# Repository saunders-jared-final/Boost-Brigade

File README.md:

# Boost Brigade — solar power shuffler (S-PPC) string

Adaptive control of serial partial-power converters ("power shufflers") for
MPPT under partial shading. QUT EGH490 capstone: control stream (this repo's
firmware/control/simulation) + hardware stream (Version 0 PCB).

**Current goal (due Fri 16 Oct 2026): carpark experiment** — 3 × 150 W panels,
2 shufflers on the Version 0 board, EcoFlow DELTA 2 Max as the string MPPT
load, closed-loop module equalisation on the Nucleo-G474RE, telemetry on
Grafana via the Raspberry Pi pod. Day-by-day plan: `0_Documentation/PLAN.md`.

## Layout

| Folder | What |
|---|---|
| `0_Documentation/` | proposals, progress reports, UI pod wiring, **`telemetry.md`** (Nucleo↔Pi contract), plan, experiment checklist |
| `1_Datasheets/` | INA239, TMCS1126, 1ED3140, EcoFlow, LM5180 calculator |
| `2_Qspice/` | switching-level models; `Claude's outputs/PCB_Baseline/` is the scripted baseline (`gen_shuffler.py` → stages S1–S8b, `run_baseline.py`); closed-loop C-block stage S9 to come |
| `3_Analytical/` | notebooks + design log (`shuffler_notebooks/DESIGN_LOG.md`) and the early MATLAB control-design lineage |
| `4_Simulink/` | test ladder: `1_MIL` (4-mod validated model), `2_SIL` (C Caller model + **host build/tests of the C core**), **`3_Carpark_3mod`** (3-module scripts + model-edit checklist) |
| `5_Kicad/` | `Version 0 project/` (schematic, PCB, gerbers) + `libs/` (all part libraries; project-relative lib tables) |
| `6_RTOS/` | STM32G474 firmware (CubeMX + CMake) and **`ctrl_core/`**, the single copy of the control-stack C shared by SIL, QSPICE and firmware; `ctrl_core/params/` holds the JSON gain file and generators |
| `7_Pi/` | Raspberry Pi pod: InfluxDB + Grafana compose, serial bridge, IR/LCD/LED service, bench tools |

## Gain flow (one source, three harnesses)

```
Simulink ident (4_Simulink/3_Carpark_3mod/shuffler_string_ident.m)
   └─> 6_RTOS/ctrl_core/params/shuffler_params.json   (M, Ts, thresholds)
         └─> gen_params.py / export_params.m  ->  6_RTOS/ctrl_core/params.h
               ├─> SIL: C Caller blocks + golden replay + unit tests (4_Simulink/2_SIL.../firmware)
               ├─> QSPICE: shuffler_ctrl.dll C-block, stage S9 (2_Qspice)
               └─> firmware: 10 kHz control ISR on the Nucleo (6_RTOS)
```

Hardware facts that shape the control configuration (verified in `5_Kicad`):
- 3 panels / 2 converters; HRTIM pins PA8-11 (S1 A/B high/low) and PB12-15 (S2); hall sensors PA0 ILA_1, PA4 ILB_1, PA1 ILA_2, PC1 ILB_2; INA239 ×3 on SPI3 (CS PA7, PB6, PC7).
- The INA239s read bus voltage only (shunt inputs shorted): module currents are **reconstructed** from the inductor currents and duties (`ctrl_core/shuffler_recon.c`); the string current is an unobservable common offset that the supervisor's deficit term cancels. String-level MPPT is the EcoFlow's job (`en_mppt = 0` in firmware).
- U10 (panel-1 voltage) sits behind a mis-wired ISO7762: rework required for closed loop on converter 1.
- 1ED3140 drivers have no fault pins and add no dead time; dead time (200 ns, HRTIM) and over-current trips are firmware.

## Quick starts

Host tests of the control core (WSL):
```sh
cd 4_Simulink/2_SIL_Software_In_The_Loop/firmware && cmake -B build && cmake --build build && ctest --test-dir build --output-on-failure
```
Regenerate gains after an identification: `python3 6_RTOS/ctrl_core/params/gen_params.py`
(or `export_params` in MATLAB). Preset `params/mil4_params.json` reproduces the validated 4-module constants.

Firmware build (Windows ST bundle, callable from WSL; paths in `6_RTOS/.vscode/tasks.json`):
```sh
cd 6_RTOS && cmake.exe --preset Debug && cmake.exe --build --preset Debug
STM32_Programmer_CLI.exe -c port=SWD -w build/Debug/Shuffler_1_Open_Loop.elf -rst
```

## Panel reference (150 W hard-frame, 22 V model)

Pm 150 W ±3 %, Vmp 18.28 V, Imp 8.207 A, Voc 22.407 V, Isc 8.721 A, NOCT 45 ±2 °C,
max series fuse 15 A, 1160 × 670 × 30 mm, 9.32 kg, IP67.

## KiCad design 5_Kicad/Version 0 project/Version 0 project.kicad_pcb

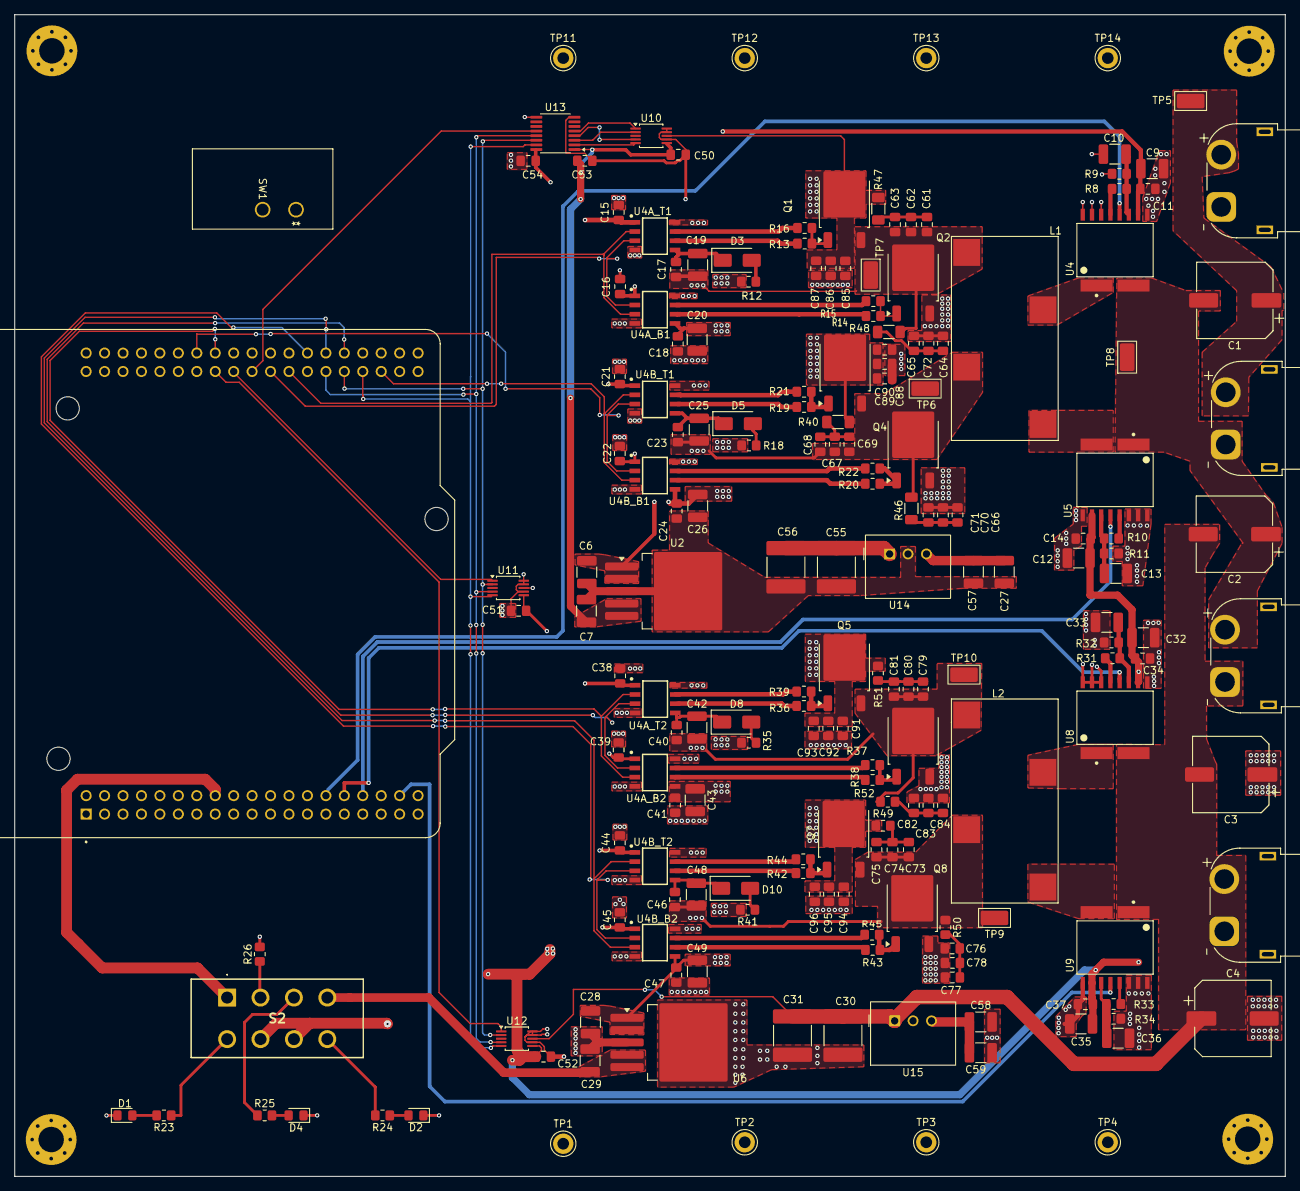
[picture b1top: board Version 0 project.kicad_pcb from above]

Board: 6 copper layers, 175.0 x 160.0 mm, 195 parts (0 on the bottom side), 96 nets.

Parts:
C1, C2: B40910A0137M000; CP_Elec_10x16.5
C3, C4: 130u; CP_Elec_10x16.5
C6, C7, C9, C10, C12, C13, C27, C28, C29, C32, C33, C35, C36, C57, C58, C59: 10uF; C_1210_3225Metric_Pad1.33x2.70mm_HandSolder
C11, C14, C34, C37, C61, C62, C63, C64, C65, C66, C67, C68, C69, C70, C71, C72, C73, C74, C75, C76, C77, C78, C79, C80, C81, C82, C83, C84, C85, C86, C87, C88, C89, C90, C91, C92, C93, C94, C95, C96: 0.1uF; C_0805_2012Metric_Pad1.18x1.45mm_HandSolder
C15, C16, C17, C18, C21, C22, C38, C39, C40, C41, C44, C45, C50, C51, C52, C53, C54: 100n; C_0805_2012Metric_Pad1.18x1.45mm_HandSolder
C19, C20, C25, C26, C42, C43, C48, C49: 10u; C_1210_3225Metric_Pad1.33x2.70mm_HandSolder
C23, C24, C46, C47: 100nF; C_0805_2012Metric_Pad1.18x1.45mm_HandSolder
C30, C31, C55, C56: 10uF; C_2220_5750Metric_Pad1.97x5.40mm_HandSolder
D1: LED_R; LED_0805_2012Metric_Pad1.15x1.40mm_HandSolder
D2: LED_B; LED_0805_2012Metric_Pad1.15x1.40mm_HandSolder
D3, D5, D8, D10: D; D_SMA
D4: LED_G; LED_0805_2012Metric_Pad1.15x1.40mm_HandSolder
H1, H2, H3, H4: MountingHole; MountingHole_3.5mm_Pad_Via
L1, L2: ERUC23-4R1K
Q1, Q2, Q3, Q4, Q5, Q6, Q7, Q8: STD45N10F7; TO-252-3_TabPin2
R8, R10, R26, R31, R33: 1k; R_0805_2012Metric_Pad1.20x1.40mm_HandSolder
R9, R11, R32, R34: 1.5K; R_0805_2012Metric_Pad1.20x1.40mm_HandSolder
R12, R13, R14, R18, R19, R20, R35, R36, R37, R41, R42, R43: 10R; R_0805_2012Metric_Pad1.20x1.40mm_HandSolder
R15, R16, R21, R22, R38, R39, R44, R45, R49, R50, R51, R52: 4.7R; R_0805_2012Metric_Pad1.20x1.40mm_HandSolder
R23, R25: 680; R_0805_2012Metric_Pad1.20x1.40mm_HandSolder
R24: 100; R_0805_2012Metric_Pad1.20x1.40mm_HandSolder
R40, R46, R47, R48: 4.7R; R_1206_3216Metric_Pad1.30x1.75mm_HandSolder
S2: L203011MS02Q
SW1: L101011MS02Q; SW_1MS02Q_CNK
TP1, TP2, TP3, TP4, TP11, TP12, TP13, TP14: TestPoint; TestPoint_Keystone_5010-5014_Multipurpose
TP5, TP6, TP7, TP8, TP9, TP10: TestPoint; TestPoint_Keystone_5019_Miniature_Wide
U1: NUCLEO-G474RE; MODULE_NUCLEO-G474RE
U2, U6: TPS7A4533; TO-263-5_TabPin3
U4, U8: TMCS1126B4AQDVGRQ1; DVG0010A-MFG
U4A_B1, U4A_B2, U4A_T1, U4A_T2, U4B_B1, U4B_B2, U4B_T1, U4B_T2: 1ED3140MU12F; SOIC127P600X175-8N-22-V1
U5, U9: TMCS1126B1AQDVGR; DVG0010A-MFG
U10, U11, U12: INA229; TSSOP-10_3x3mm_P0.5mm
U13: ISO7762QDBQRQ1; SSOP-16_3.9x4.9mm_P0.635mm
U14, U15: 173951275; U_Wurth_WPME-FDSM_17395xx75
XT60_1: PV Connector 1; AMASS_XT60PW-F_1x02_P7.20mm_Horizontal
XT60_2: PV Connector 2; AMASS_XT60PW-F_1x02_P7.20mm_Horizontal
XT60_3: PV Connector 3; AMASS_XT60PW-F_1x02_P7.20mm_Horizontal
XT60_4: PV Connector 4; AMASS_XT60PW-F_1x02_P7.20mm_Horizontal

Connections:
+3V3: C9.1, C11.1, C12.1, C14.1, C32.1, C34.1, C35.1, C37.1, C51.1, C52.1, C54.2, S2.6, S2.7, SW1.1, U4.4 (VS), U5.4 (VS), U8.4 (VS), U9.4 (VS), U11.6 (VS), U12.6 (VS), U13.16 (Vcc2)
/CS1: U1.CN10_15 (PA7), U12.1 (~CS)
/CS2: U1.CN10_17 (PB6), U11.1 (~CS)
/CS3: U1.CN10_19 (PC7), U13.12 (OUTD)
/Floating 3v3: C7.1, C50.1, C53.1, U2.4 (OUT), U2.5 (SENSE), U10.6 (VS), U13.1 (Vcc1)
/Gate Driver 3v3: C15.2, C16.2, C21.2, C22.2, C38.2, C39.2, C44.2, C45.2, SW1.2, U4A_B1.1 (VCC1), U4A_B2.1 (VCC1), U4A_T1.1 (VCC1), U4A_T2.1 (VCC1), U4B_B1.1 (VCC1), U4B_B2.1 (VCC1), U4B_T1.1 (VCC1), U4B_T2.1 (VCC1)
/ILA_1: U1.CN7_28 (PA0), U4.6 (VOUT)
/ILA_2: U1.CN7_30 (PA1), U8.6 (VOUT)
/ILB_1: U1.CN7_32 (PA4), U5.6 (VOUT)
/ILB_2: U1.CN7_36 (PC1/PB9), U9.6 (VOUT)
/LDO 3v3: C29.1, S2.4, U6.4 (OUT), U6.5 (SENSE)
/S1_A_H: U1.CN10_23 (PA8), U4A_B1.3 (IN_N), U4A_T1.2 (IN_P)
/S1_A_L: U1.CN10_21 (PA9), U4A_B1.2 (IN_P), U4A_T1.3 (IN_N)
/S1_B_H: U1.CN10_33 (PA10), U4B_B1.3 (IN_N), U4B_T1.2 (IN_P)
/S1_B_L: U1.CN10_14 (PA11), U4B_B1.2 (IN_P), U4B_T1.3 (IN_N)
/S2_A_H: U1.CN10_16 (PB12), U4A_B2.3 (IN_N), U4A_T2.2 (IN_P)
/S2_A_L: U1.CN10_30 (PB13), U4A_B2.2 (IN_P), U4A_T2.3 (IN_N)
/S2_B_H: U1.CN10_28 (PB14), U4B_B2.3 (IN_N), U4B_T2.2 (IN_P)
/S2_B_L: U1.CN10_26 (PB15), U4B_B2.2 (IN_P), U4B_T2.3 (IN_N)
/SPI MISO: U1.CN10_27 (PB4), U11.4 (MISO), U12.4 (MISO), U13.13 (OUTC)
/SPI MOSI: U1.CN10_29 (PB5), U11.2 (MOSI), U12.2 (MOSI), U13.14 (OUTB)
/SPI SCLK: U1.CN10_31 (PB3), U11.5 (SCLK), U12.5 (SCLK), U13.15 (OUTA)
/Shuffle Converter 1/L_Aph2: L1.1, U4.1 (IN+)
/Shuffle Converter 1/L_Bph2: L1.2, U5.2 (IN-)
/Shuffle Converter 1/M_B_Aph_G: Q2.1 (G), R14.2, R15.2
/Shuffle Converter 1/M_B_Bph_G: Q4.1 (G), R20.2, R22.2
/Shuffle Converter 1/M_T_Aph_G: Q1.1 (G), R13.2, R16.2
/Shuffle Converter 1/M_T_Aph_S: C17.2, C19.2, C61.2, C62.2, C63.2, L1.4, Q1.3 (S), Q2.2 (D), R48.1, TP7.1 (1_1), U4A_T1.8 (VEE2)
/Shuffle Converter 1/M_T_Bph_G: Q3.1 (G), R19.2, R21.2
/Shuffle Converter 1/M_T_Bph_S: C23.2, C25.2, C67.2, C68.2, C69.2, L1.3, Q3.3 (S), Q4.2 (D), R46.1, TP6.1 (1_1), U4B_T1.8 (VEE2)
/Shuffle Converter 1/Vreg_Output: C6.1, C18.1, C20.1, C24.1, C26.1, C27.1, C57.1, R12.2, R18.2, U2.1 (~SHDN), U2.2 (IN), U4A_B1.5 (VCC2), U4B_B1.5 (VCC2), U14.3 (VOUT)
/Shuffle Converter 2/L_Aph2: L2.1, U8.1 (IN+)
/Shuffle Converter 2/L_Bph2: L2.2, U9.2 (IN-)
/Shuffle Converter 2/M_B_Aph_G: Q6.1 (G), R37.2, R38.2
/Shuffle Converter 2/M_B_Bph_G: Q8.1 (G), R43.2, R45.2
/Shuffle Converter 2/M_T_Aph_G: Q5.1 (G), R36.2, R39.2
/Shuffle Converter 2/M_T_Aph_S: C40.2, C42.2, C79.2, C80.2, C81.2, L2.4, Q5.3 (S), Q6.2 (D), R52.1, TP10.1 (1_1), U4A_T2.8 (VEE2)
/Shuffle Converter 2/M_T_Bph_G: Q7.1 (G), R42.2, R44.2
/Shuffle Converter 2/M_T_Bph_S: C46.2, C48.2, C73.2, C74.2, C75.2, L2.3, Q7.3 (S), Q8.2 (D), R50.1, TP9.1 (1_1), U4B_T2.8 (VEE2)
/Shuffle Converter 2/Vreg_Output: C28.1, C41.1, C43.1, C47.1, C49.1, C58.1, C59.1, R35.2, R41.2, U4A_B2.5 (VCC2), U4B_B2.5 (VCC2), U6.1 (~SHDN), U6.2 (IN), U15.3 (VOUT)
GND: C4.2, C9.2, C10.2, C11.2, C12.2, C13.2, C14.2, C15.1, C16.1, C21.1, C22.1, C28.2, C29.2, C30.2, C31.2, C32.2, C33.2, C34.2, C35.2, C36.2, C37.2, C38.1, C39.1, C41.2, C43.2, C44.1, C45.1, C47.2, C49.2, C51.2, C52.2, C54.1, C58.2, C59.2, C76.2, C77.2, C78.2, C82.2, C83.2, C84.2, C91.2, C92.2, C93.2, C94.2, C95.2, C96.2, D1.1 (K), D2.1 (K), D4.1 (K), Q6.3 (S), Q8.3 (S), R9.2, R11.2, R26.2, R32.2, R34.2, TP1.1 (1_1), TP2.1 (1_1), TP3.1 (1_1), TP4.1 (1_1), TP11.1 (1_1), TP12.1 (1_1), TP13.1 (1_1), TP14.1 (1_1), U4.3 (OC_N), U4.8 (NC), U4.9 (GND), U4.10 (NC), U4A_B1.4 (GND1), U4A_B2.4 (GND1), U4A_B2.8 (VEE2), U4A_T1.4 (GND1), U4A_T2.4 (GND1), U4B_B1.4 (GND1), U4B_B2.4 (GND1), U4B_B2.8 (VEE2), U4B_T1.4 (GND1), U4B_T2.4 (GND1), U5.3 (OC_N), U5.8 (NC), U5.9 (GND), U5.10 (NC), U6.3 (GND), U8.3 (OC_N), U8.8 (NC), U8.9 (GND), U8.10 (NC), U9.3 (OC_N), U9.8 (NC), U9.9 (GND), U9.10 (NC), U11.7 (GND), U11.9 (IN-), U11.10 (IN+), U12.7 (GND), U12.9 (IN-), U12.10 (IN+), U13.9 (GND2), U15.2 (GND), XT60_3.1 (Pin_2), XT60_4.1 (Pin_2)
unnamed: C61.1, C62.1, C63.1, R47.2
unnamed: C64.1, C65.1, C72.1, R48.2
unnamed: C66.1, C70.1, C71.1, R46.2
unnamed: C67.1, C68.1, C69.1, R40.2
unnamed: C73.1, C74.1, C75.1, R49.2
unnamed: C76.1, C77.1, C78.1, R50.2
unnamed: C79.1, C80.1, C81.1, R51.2
unnamed: C82.1, C83.1, C84.1, R52.2
unnamed: D1.2 (A), R23.2
unnamed: D2.2 (A), R24.1
unnamed: D3.2 (A), R12.1
unnamed: C17.1, C19.1, D3.1 (K), U4A_T1.5 (VCC2)
unnamed: D4.2 (A), R25.2
unnamed: D5.2 (A), R18.1
unnamed: C23.1, C25.1, D5.1 (K), U4B_T1.5 (VCC2)
unnamed: D8.2 (A), R35.1
unnamed: C40.1, C42.1, D8.1 (K), U4A_T2.5 (VCC2)
unnamed: D10.2 (A), R41.1
unnamed: C46.1, C48.1, D10.1 (K), U4B_T2.5 (VCC2)
unnamed: R23.1, S2.5
unnamed: R24.2, S2.8
unnamed: R25.1, S2.3
unnamed: R26.1, S2.2
unnamed: S2.1, U1.CN7_16 (+3V3)
unnamed: C10.1, R8.2, R9.1, U4.5 (VOC)
unnamed: R8.1, U4.7 (VREF)
unnamed: R14.1, U4A_B1.6 (OUTH)
unnamed: R15.1, U4A_B1.7 (OUTL)
unnamed: R37.1, U4A_B2.6 (OUTH)
unnamed: R38.1, U4A_B2.7 (OUTL)
unnamed: R13.1, U4A_T1.6 (OUTH)
unnamed: R16.1, U4A_T1.7 (OUTL)
unnamed: R36.1, U4A_T2.6 (OUTH)
unnamed: R39.1, U4A_T2.7 (OUTL)
unnamed: R20.1, U4B_B1.6 (OUTH)
unnamed: R22.1, U4B_B1.7 (OUTL)
unnamed: R43.1, U4B_B2.6 (OUTH)
unnamed: R45.1, U4B_B2.7 (OUTL)
unnamed: R19.1, U4B_T1.6 (OUTH)
unnamed: R21.1, U4B_T1.7 (OUTL)
unnamed: R42.1, U4B_T2.6 (OUTH)
unnamed: R44.1, U4B_T2.7 (OUTL)
unnamed: C13.1, R10.2, R11.1, U5.5 (VOC)
unnamed: R10.1, U5.7 (VREF)
unnamed: C33.1, R31.2, R32.1, U8.5 (VOC)
unnamed: R31.1, U8.7 (VREF)
unnamed: C36.1, R33.2, R34.1, U9.5 (VOC)
unnamed: R33.1, U9.7 (VREF)
unnamed: U10.4 (MISO), U13.4 (INC)
unnamed: U10.2 (MOSI), U13.3 (INB)
unnamed: U10.5 (SCLK), U13.2 (INA)
unnamed: U10.1 (~CS), U13.5 (IND)
PV1+: C1.1, C85.1, C86.1, C87.1, C88.1, C89.1, C90.1, Q1.2 (D), Q3.2 (D), R40.1, R47.1, TP5.1 (1_1), U10.8 (VBUS), XT60_1.2 (Pin_1), XT60_4.2 (Pin_1)
PV2+: C1.2, C2.1, C3.1, C55.1, C56.1, C91.1, C92.1, C93.1, C94.1, C95.1, C96.1, Q5.2 (D), Q7.2 (D), R49.1, R51.1, TP8.1 (1_1), U4.2 (IN-), U5.1 (IN+), U11.8 (VBUS), U14.1 (VIN), XT60_1.1 (Pin_2), XT60_2.2 (Pin_1)
PV3+: C2.2, C3.2, C4.1, C6.2, C7.2, C18.2, C20.2, C24.2, C26.2, C27.2, C30.1, C31.1, C50.2, C53.2, C55.2, C56.2, C57.2, C64.2, C65.2, C66.2, C70.2, C71.2, C72.2, C85.2, C86.2, C87.2, C88.2, C89.2, C90.2, Q2.3 (S), Q4.3 (S), U2.3 (GND), U4A_B1.8 (VEE2), U4B_B1.8 (VEE2), U8.2 (IN-), U9.1 (IN+), U10.7 (GND), U10.9 (IN-), U10.10 (IN+), U12.8 (VBUS), U13.8 (GND1), U14.2 (GND), U15.1 (VIN), XT60_2.1 (Pin_2), XT60_3.2 (Pin_1)

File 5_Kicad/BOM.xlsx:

PCB Component Reference Labels | Part Number | Description | Quantity | Unit Cost (AUD) | Gross Cost (AUD) | Shopping Cart | URLs
U14,U15 | 173951275 | For optimal performance the module is recommended for use with an external inpu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 | 3 | 7.5 | 22.5 | 1 | 173951275 Würth Elektronik | DC DC Converters | DigiKey
R24 | 100R | 100R Resistor | 1 | 0.15 | 0.15 | 1 | RK73H2ATTD1000F KOA Speer Electronics, Inc. | Chip Resistor - Surface Mount | D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
C6,C7,C9,C10,C12,C13,C27,C28,C29,C32,C33,C35,C36,C57,C58,C59, C19,C20,C25,C26,C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 | 12105C106KAT2A | 10uF Unpolarized capacitor, small symbol | 25 | 1.042 | 26.05 | 1 | 12105C106KAT2A KYOCERA AVX | Ceramic Capacitors | DigiKey
U4A_B1,U4A_B2,U4A_T1,U4A_T2,U4B_B1,U4B_B2,U4B_T1,U4B_T2 | 1ED3140MU12F | Single Channel Isolated Gate Driver IC with Separate Output | 8 | 2.4300000000000002 | 19.440000000000001 | 1 | 1ED3140MU12FXUMA1 Infineon Technologies | Isolators - Gate Drivers | DigiKey
R23,R25 | 680R | 680R Resistor | 4 |  | 0 | 1 | RK73H2ATTD6800F KOA Speer Electronics, Inc. | Chip Resistor - Surface Mount | D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
C1,C2,C3, C4 | B40910A0137M000 | 130u Unpolarized capacitor | 4 | 5.07 | 20.28 | 0 | B40910A0137M000 TDK | Aluminum - Polymer Capacitors | DigiKey
C30,C31,C55,C56 | C5750X7S2A106K230KB | Larger 10uF cap for Isolated Supply IC | 6 | 3.47 | 20.82 | 1 | C5750X7S2A106K230KB TDK | Ceramic Capacitors | DigiKey
R8,R10,R26,R31,R33 | ERA-6AEB102V | 1k Resistor | 8 | 0.15 | 1.2 | 1 | ERA-6AEB102V Panasonic Industry | Chip Resistor - Surface Mount | DigiKey
R9,R11,R32,R34 | ERA-6AEB152V | 1.5k Resistor | 6 | 0.15 | 0.89999999999999991 | 1 | ERA-6AEB152V Panasonic Industry | Chip Resistor - Surface Mount | DigiKey
L1,L2 | ERUC23-4R1K | Coupled inductor | 2 | 14.73 | 29.46 | 0 | ERUC23-4R1K TDK | Arrays, Signal Transformers | DigiKey
U10,U11,U12 | INA239 | IC PWR MONITOR 10VSSOP | 5 | 7.32 | 36.6 | 1 | INA239AQDGSRQ1 Texas Instruments | Power Supply Controllers, Monitors | DigiKey
U13 | ISO7762QDBQRQ1 | Default high, High-speed, robust EMC, reinforced, six-channel, digital, isolato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 | 2 | 5.81 | 11.62 | 1 | ISO7762QDBQRQ1 Texas Instruments | Digital Isolators | DigiKey
C11,C14,C34,C37,C61,C62,C63,C64,C65,C66,C67,C68,C69,C70,C71,C72,C73,C74,C75,C76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 | KGM21NR71H104KM | 100nF capacitor | 50 | 0.38700000000000001 | 19.350000000000001 | 1 | https://www.digikey.com.au/en/products/detail/kyocera-avx/kg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
SW1 | L101011MS02Q |  | 2 | 6.13 | 12.26 | 0 | L101011MS02Q C&K | Slide Switches | DigiKey
S2 | L203011MS02Q | Slide Switch DP3T Through Hole, Voltage Rating - DC 28 V, 4A, -30C ~ 65C | 2 | 11.07 | 22.14 | 1 | L203011MS02Q C&K | Slide Switches | DigiKey Marketplace
D1 | LSM0805412V | Red Light emitting diode | 2 | 0.54 | 1.08 | 1 | LSM0805412V Visual Communications Company - VCC | LED Indication - Discrete | D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
D4 | LSM0805452V | Green Light emitting diode | 2 | 0.41 | 0.82 | 1 | LSM0805452V Visual Communications Company - VCC | LED Indication - Discrete | D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
D2 | LSM0805463V | Blue Light emitting diode | 2 | 0.66 | 1.32 | 1 | LSM0805463V Visual Communications Company - VCC | LED Indication - Discrete | D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
U1 | NUCLEO-G474RE | STM32G474 Nucleo-64 STM32G4 ARMÂ® CortexÂ®-M4 MCU 32-Bit Embedded Evaluation Bo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 | 1 | 29.31 | 29.31 | 0 | NUCLEO-G474RE STMicroelectronics | Embedded MCU, DSP Evaluation Boards | DigiKey
XT60_1, XT60_2, XT60_3, XT60_4 | PV Connector 1 - 4 | Generic connector, single row, 01x02, script generated (kicad-library-utils/sch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 | 4 |  | 27.65 | 1 | 5 Pairs Amass XT60 XT60PW Male Female Plug Connector Adapter for RC Battery : A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
R15,R16,R21,R22,R38,R39,R40,R44,R45,R46,R47,R48,R49,R50,R51,R52 | SG73P2ATTD4R70F | 4R7 Resistor | 18 | 0.25 | 4.5 | 1 | SG73P2ATTD4R70F KOA Speer Electronics, Inc. | Chip Resistor - Surface Mount | D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
R12,R13,R14,R18,R19,R20,R35,R36,R37,R41,R42,R43 | SG73S2ATTD10R0F | 10R Resistor | 14 | 0.25 | 3.5 | 1 | SG73S2ATTD10R0F KOA Speer Electronics, Inc. | Chip Resistor - Surface Mount | D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
Q1,Q2,Q3,Q4,Q5,Q6,Q7,Q8 | STD45N10F7 | N-MOSFET transistor, gate/drain/source | 12 | 3.12 | 37.44 | 1 | STD45N10F7 STMicroelectronics | Single FETs, MOSFETs | DigiKey
TP1,TP2,TP3,TP4,TP11,TP12,TP13,TP14 | TestPoint | test point tht | 16 |  | 0 | 1 | 5014 Keystone Electronics | Test Points | DigiKey
TP5,TP6,TP7,TP8,TP9,TP10 | TestPoint | test point smd | 10 |  | 0 | 1 | 5019 Keystone Electronics | Test Points | DigiKey
U4, U5, U8, U9 | TMCS1126B4AQDVGRQ1 | CURRENT SEN HALL EFFECT 10-SOIC | 6 | 7.35 | 44.099999999999994 | 1 | TMCS1126B4AQDVGRQ1 Texas Instruments | Current Sensors | DigiKey
U2,U6, U5,U9 | TPS7A4533KTTR | Low-Noise Fast-Transient-Response 1.5A LDO Regulator, Fixed Output, Vin = 20V m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 | 4 | 3.76 | 15.04 | 1 | TPS7A4533KTTR Texas Instruments | Voltage Regulators - Linear, Low Drop Out (LD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
D3,D5,D8,D10 | VSSA210-E3/61T | 100V, Schottky Bootstrapping diode (SMA) | 6 | 0.95 | 5.6999999999999993 | 1 | VSSA210-E3/61T Vishay General Semiconductor - Diodes Division | Single Diodes |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
 | 28 |  |  |  |  | 1
 |  | Total | 225 |  | 413.2299999999999 | 321.92000000000007
 |  |  |  |  |  | 91.309999999999832

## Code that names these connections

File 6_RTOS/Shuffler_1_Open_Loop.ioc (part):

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Mcu.Name=STM32G474R(B-C-E)Tx
Mcu.Package=LQFP64
Mcu.UserName=STM32G474RETx
PA0.GPIOParameters=GPIO_Label
PA0.GPIO_Label=ILA_1
PA0.Mode=IN1-Single-Ended
PA0.Signal=ADC1_IN1
PA1.GPIOParameters=GPIO_Label
PA1.GPIO_Label=ILA_2
PA1.Mode=IN2-Single-Ended
PA1.Signal=ADC1_IN2
PA10.GPIOParameters=GPIO_Label
PA10.GPIO_Label=S1_B_H
PA10.Signal=GPIO_Output
PA11.GPIOParameters=GPIO_Label
PA11.GPIO_Label=S1_B_L
PA11.Signal=GPIO_Output
PA13.GPIOParameters=GPIO_Label
PA13.GPIO_Label=T_SWDIO
PA13.Signal=SYS_JTMS-SWDIO
PA14.GPIOParameters=GPIO_Label
PA14.GPIO_Label=T_SWCLK
PA14.Signal=SYS_JTCK-SWCLK
PA2.Signal=LPUART1_TX
PA3.Signal=LPUART1_RX
PA4.GPIOParameters=GPIO_Label
PA4.GPIO_Label=ILB_1
PA4.Mode=IN17-Single-Ended
PA4.Signal=ADC2_IN17
PA7.GPIOParameters=PinState,GPIO_Label
PA7.GPIO_Label=INA_CS1
PA7.PinState=GPIO_PIN_SET
PA7.Signal=GPIO_Output
PA8.GPIOParameters=GPIO_Label
PA8.GPIO_Label=S1_A_H
PA8.Signal=GPIO_Output
PA9.GPIOParameters=GPIO_Label
PA9.GPIO_Label=S1_A_L
PA9.Signal=GPIO_Output
PB12.GPIOParameters=GPIO_Label
PB12.GPIO_Label=S2_A_H
PB12.Mode=Output_TC1TC2
PB12.Signal=HRTIM1_CHC1
PB13.GPIOParameters=GPIO_Label
PB13.GPIO_Label=S2_A_L
PB13.Mode=Output_TC1TC2
PB13.Signal=HRTIM1_CHC2
PB14.GPIOParameters=GPIO_Label
PB14.GPIO_Label=S2_B_H
PB14.Mode=Output_TD1TD2
PB14.Signal=HRTIM1_CHD1
PB15.GPIOParameters=GPIO_Label
PB15.GPIO_Label=S2_B_L
PB15.Mode=Output_TD1TD2
PB15.Signal=HRTIM1_CHD2
PB3.Mode=Full_Duplex_Master
PB3.Signal=SPI3_SCK
PB4.Mode=Full_Duplex_Master
PB4.Signal=SPI3_MISO
PB5.Mode=Full_Duplex_Master
PB5.Signal=SPI3_MOSI
PB6.GPIOParameters=PinState,GPIO_Label
PB6.GPIO_Label=INA_CS2
PB6.PinState=GPIO_PIN_SET
PB6.Signal=GPIO_Output
PC1.GPIOParameters=GPIO_Label
PC1.GPIO_Label=ILB_2
PC1.Mode=IN7-Single-Ended
PC1.Signal=ADC2_IN7
PC14-OSC32_IN.GPIOParameters=GPIO_Label
PC14-OSC32_IN.GPIO_Label=RCC_OSC32_IN
PC14-OSC32_IN.Signal=RCC_OSC32_IN
PC15-OSC32_OUT.GPIOParameters=GPIO_Label
PC15-OSC32_OUT.GPIO_Label=RCC_OSC32_OUT
PC15-OSC32_OUT.Signal=RCC_OSC32_OUT
PC7.GPIOParameters=PinState,GPIO_Label
PC7.GPIO_Label=INA_CS3
PC7.PinState=GPIO_PIN_SET
PC7.Signal=GPIO_Output
PF0-OSC_IN.GPIOParameters=GPIO_Label
PF0-OSC_IN.GPIO_Label=RCC_OSC_IN
PF0-OSC_IN.Signal=RCC_OSC_IN
PF1-OSC_OUT.GPIOParameters=GPIO_Label
PF1-OSC_OUT.GPIO_Label=RCC_OSC_OUT
PF1-OSC_OUT.Signal=RCC_OSC_OUT
RCC.HSE_VALUE=24000000
RCC.SYSCLKFreq_VALUE=170000000
RCC.SYSCLKSource=RCC_SYSCLKSOURCE_PLLCLK
board=NUCLEO-G474RE
boardIOC=true

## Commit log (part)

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2026-04-20 First commit - README
2026-04-26 1st attempt at replicating Batzelis. Unstable plots generated!
2026-05-27 your message
2026-05-27 Updated Shuffler Model
    Still needs to assess large voltage fluctuation on switching edge. 500W ripple vs 10-20W in Qspice ?
2026-05-27 Working Shuffler Simulink
    Shuffler is now working on 50% duty. Or so I think. Please verify.
2026-05-29 Playing with current control
    bruh
2026-06-30 Shuffler Control V3
    Works individually but not with other shufflers
2026-06-30 Updated 30.6.26
2026-06-30 Updated again
